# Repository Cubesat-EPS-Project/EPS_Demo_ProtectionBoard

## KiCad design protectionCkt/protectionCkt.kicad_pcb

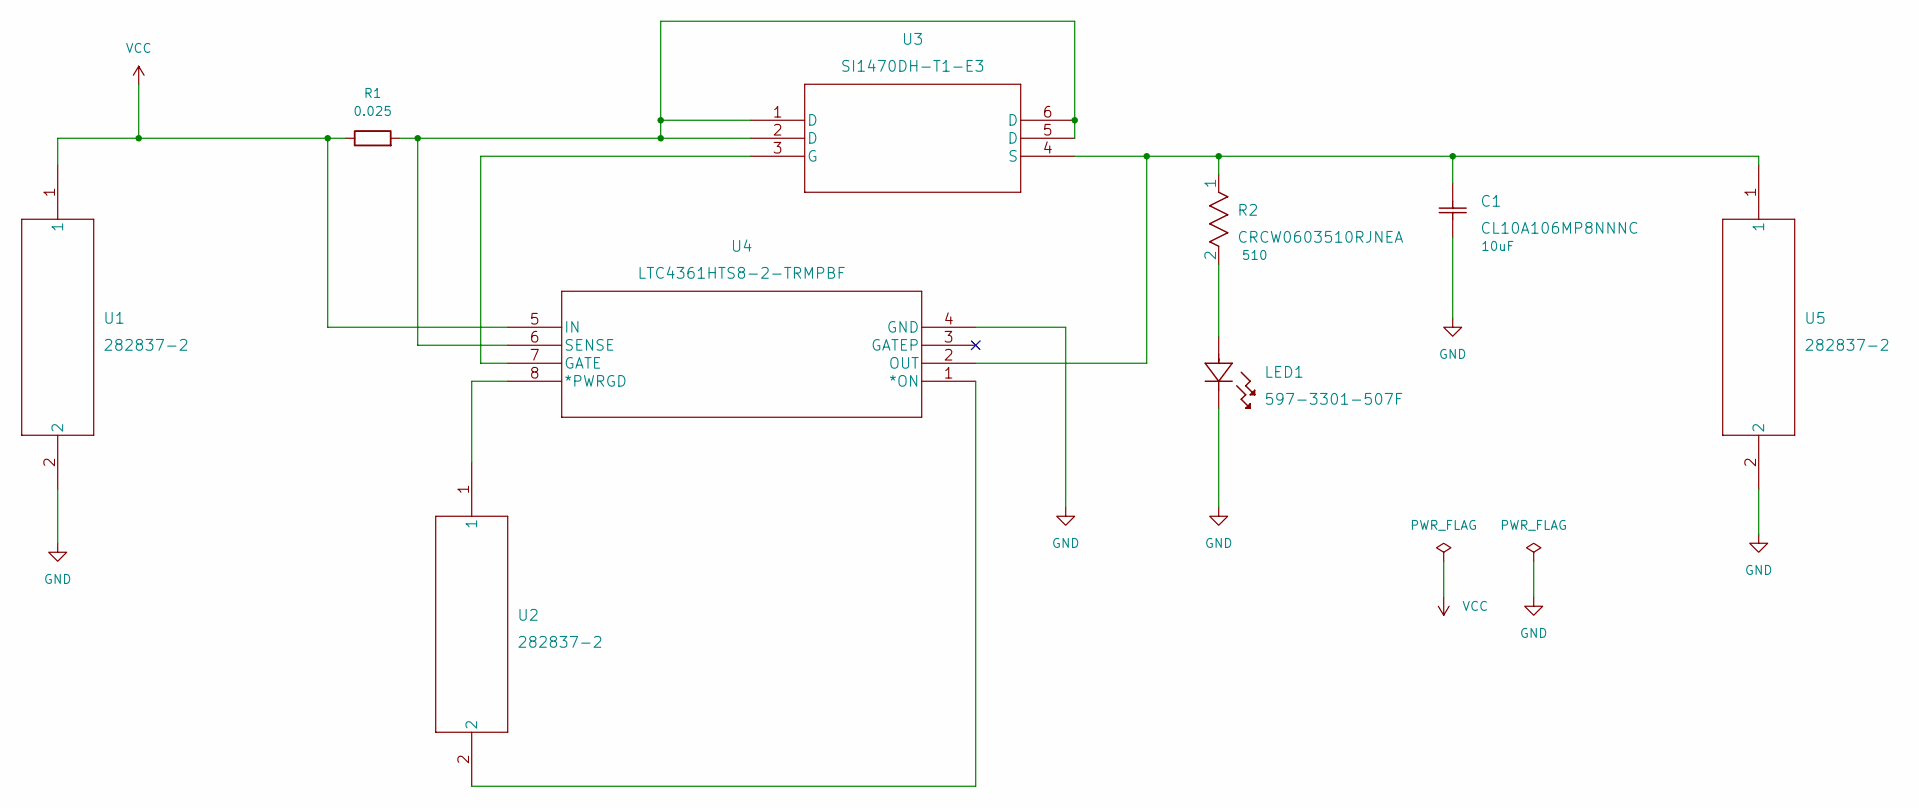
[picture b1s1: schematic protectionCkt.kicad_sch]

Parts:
C1: CL10A106MP8NNNC
LED1: 597-3301-507F
R1: 0.025; WSL0603R0510FEA
R2: CRCW0603510RJNEA
U1, U2, U5: 282837-2
U3: SI1470DH-T1-E3
U4: LTC4361HTS8-2-TRMPBF

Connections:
GND: C1.1, LED1.1, U1.2, U4.4 (GND), U5.2
unnamed: C1.2, R2.1, U3.4 (S), U4.2 (OUT), U5.1
unnamed: LED1.2, R2.2
unnamed: R1.2, U3.1 (D), U3.2 (D), U3.5 (D), U3.6 (D), U4.6 (SENSE)
unnamed: U2.1, U4.8 (*PWRGD)
unnamed: U3.3 (G), U4.7 (GATE)
unnamed: U2.2, U4.1 (*ON)
VCC: R1.1, U1.1, U4.5 (IN)

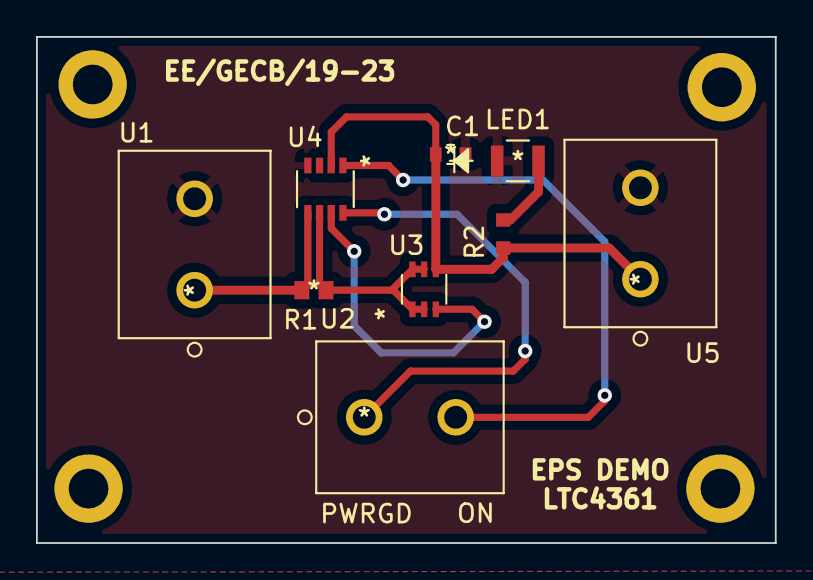
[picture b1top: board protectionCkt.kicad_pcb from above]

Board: 2 copper layers, 41.0 x 28.1 mm, 9 parts (0 on the bottom side), 8 nets.

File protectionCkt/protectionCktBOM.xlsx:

Reference | Quantity | Model | Footprint | Datasheet_link | Value | Price
C1 | 4 | CL10A106MP8NNNC | myfootprints:CL10A106MP8NNNC | https://www.mouser.in/ProductDetail/Samsung-Electro-Mechanic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 | 10uF | ₹13.84
LED1 | 4 | 597-3301-507F | myfootprints:597-3301-507F | https://www.mouser.in/ProductDetail/Dialight/597-3301-507F?q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 | - | ₹43.96
R1 | 4 | WSL0603R0250FEA | myfootprints:WSL0603R0510FEA | https://www.mouser.in/ProductDetail/Vishay-Dale/WSL0603R0510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 | 0.025? | ₹94.42
R2 | 10 | CRCW0603510RJNEA | myfootprints:CRCW0603510RJNEA | https://www.mouser.in/ProductDetail/Vishay-Dale/CRCW0603510R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 | 510? | ₹2.77
U1 U2 U5 | 10 | 282837-2 | myfootprints:282837-2 | https://www.mouser.in/ProductDetail/TE-Connectivity/282837-2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 | - | ₹53.56
U3 | 4 | SI1470DH-T1-E3 | myfootprints:SI1470DH-T1-E3 | https://www.mouser.in/ProductDetail/Vishay-Siliconix/SI1470D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 | - | not available
u3-alt | 4 | SI1416EDH-T1-GE3 | same footprint as U3 | https://www.mouser.in/ProductDetail/?qs=pNKBmB2EQRiQP6xZUEPc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 | - | ₹38.26
U4 | 4 | LTC4361HTS8-2-TRMPBF | myfootprints:LTC4361HTS8-2-TRMPBF | https://www.mouser.in/ProductDetail/Analog-Devices/LTC4361HT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 | - | ₹488.4

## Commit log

2023-01-28 Add files via upload
    The symbol libraries used for Protection circuit demo board using LTC4361 IC.
2023-01-28 Add files via upload
    The footprint libraries used for protection circuit demo board using LTC4361 IC.
2023-01-28 Add files via upload
    The gerber files of protection circuit demo board using LTC4361 IC.
2023-02-03 Final Protection Board
    added terminal for ON pin of LTC4361 IC to control the IC using microcontroller (So that we can manually control the 5v and 3.3v buses).
2023-02-04 Added BOM
    Added Bill of materials with purchase links and cost.
2023-02-10 updated pcb
    reduced pcb size, added corner chamfer.

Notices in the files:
parts and their libraries:
Copyright 2021 Accelerated Designs. All rights reserved.
